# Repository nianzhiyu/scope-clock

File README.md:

# scope-clock
A digital clock using oscilloscope CRT display.
Derived from cathode corner's design: http://www.cathodecorner.com/sc200c.html

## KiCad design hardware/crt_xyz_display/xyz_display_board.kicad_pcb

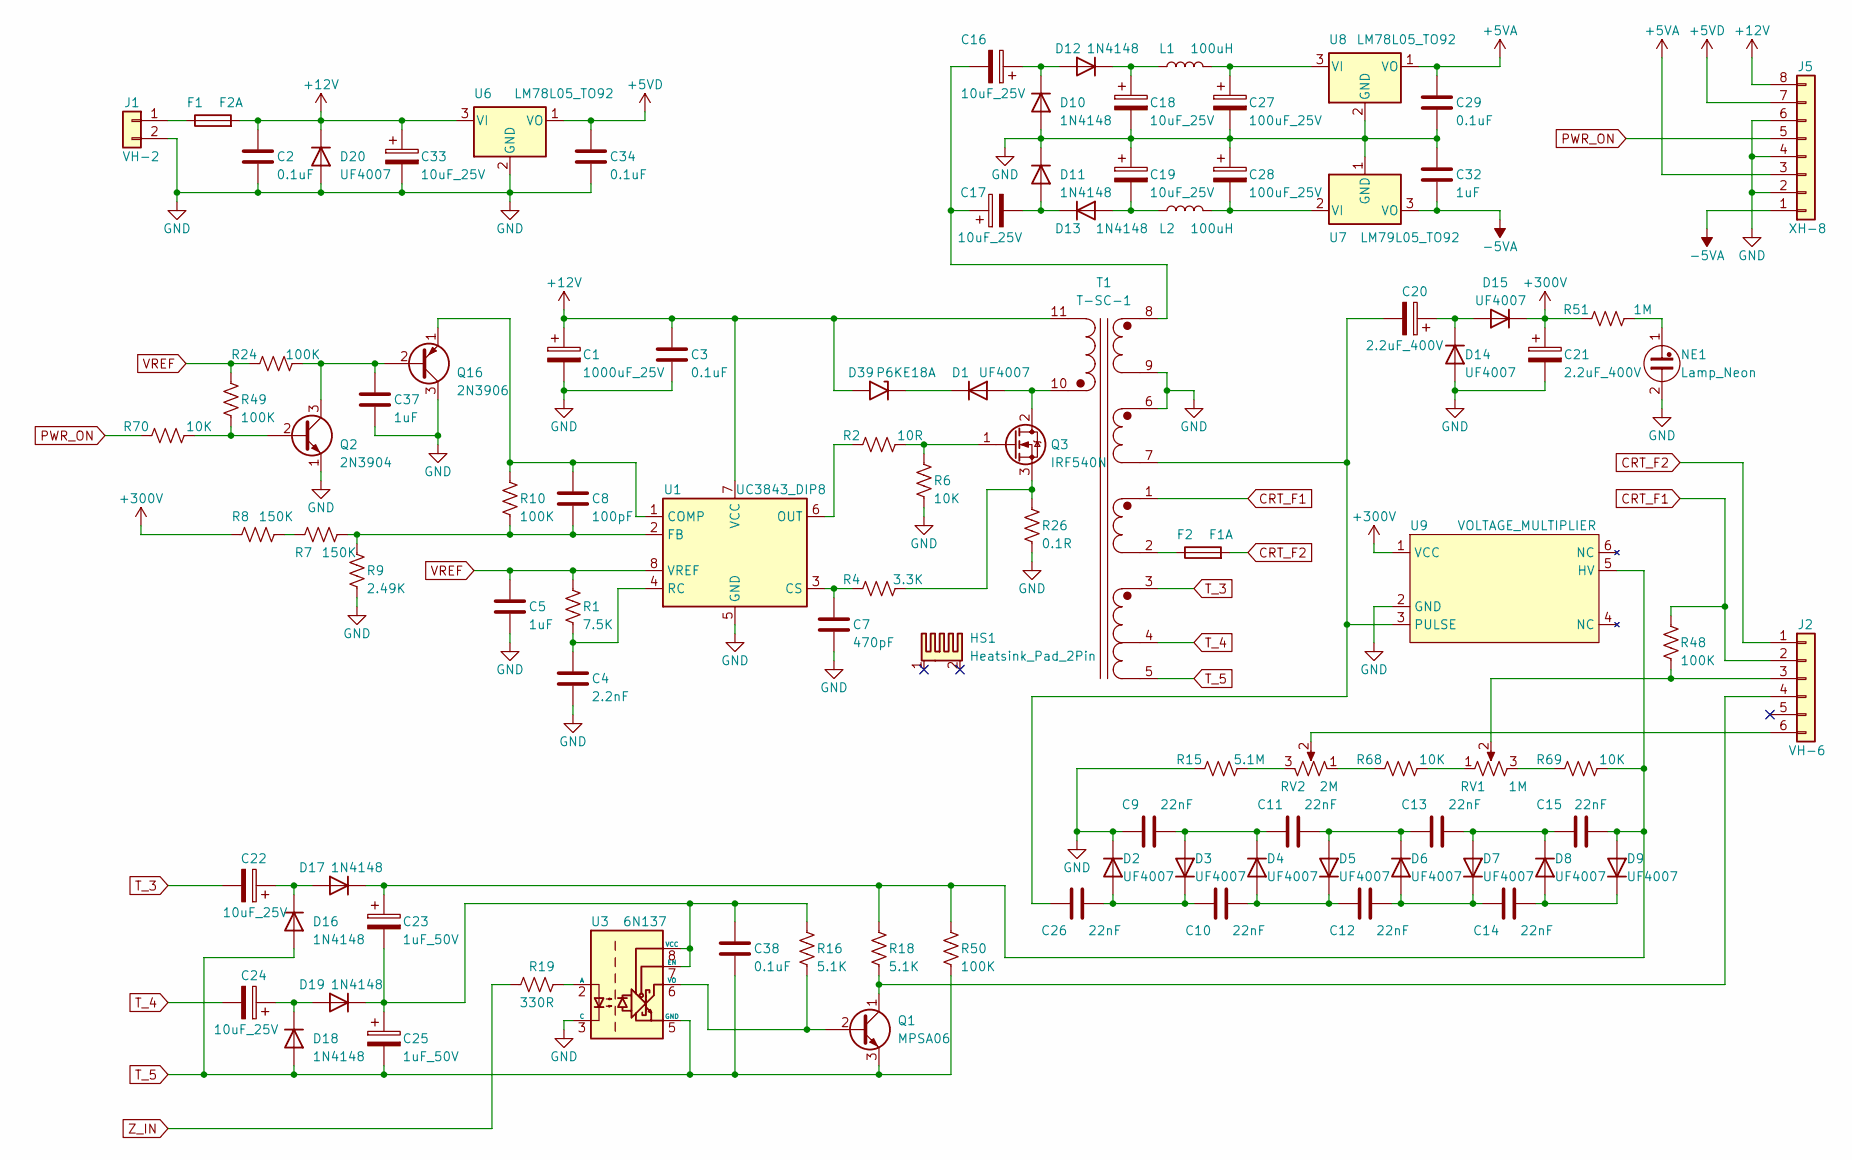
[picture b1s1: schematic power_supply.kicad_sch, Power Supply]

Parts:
C1: 1000uF_25V; CP_Radial_D10.0mm_P5.00mm
C2, C3, C29, C34, C38: 0.1uF; C_Rect_L5.5mm_W4.0mm_P5.00mm
C4: 2.2nF; C_Rect_L5.5mm_W4.0mm_P5.00mm
C5, C32, C37: 1uF; C_Rect_L5.5mm_W4.0mm_P5.00mm
C7: 470pF; C_Rect_L5.5mm_W4.0mm_P5.00mm
C8: 100pF; C_Rect_L5.5mm_W4.0mm_P5.00mm
C9, C10, C11, C12, C13, C14, C15, C26: 22nF; C_1206_3216Metric
C16, C17, C18, C19: 10uF_25V; CP_Radial_D6.3mm_P2.50mm
C20, C21: 2.2uF_400V; CP_Radial_D8.0mm_P3.50mm
C22, C24, C33: 10uF_25V; CP_Radial_D5.0mm_P2.50mm
C23, C25: 1uF_50V; CP_Radial_D5.0mm_P2.50mm
C27, C28: 100uF_25V; CP_Radial_D6.3mm_P2.50mm
D1, D2, D3, D4, D5, D6, D7, D8, D9, D14, D15, D20: UF4007; D_DO-41_SOD81_P7.62mm_Horizontal
D10, D11, D12, D13, D16, D17, D18, D19: 1N4148; DO-35-H6_8
D39: P6KE18A; D_DO-15_P10.16mm_Horizontal
F1: F2A; FUSE_D3.0mm_L8.3mm_P10.16mm
F2: F1A; FUSE_D3.0mm_L8.3mm_P10.16mm
HS1: Heatsink_Pad_2Pin; HS2-23_5X16X25
J1: VH-2; JST_VH_B2P-VH_1x02_P3.96mm_Vertical
J2: VH-6; JST_VH_B6P-VH_1x06_P3.96mm_Vertical
J5: XH-8; JST_XH_B8B-XH-A_1x08_P2.50mm_Vertical
L1, L2: 100uH; L_Radial_D5.5mm_P2.00mm
NE1: Lamp_Neon; NL_D5.0mm
Q1: MPSA06; TO-92L_Inline_Wide
Q2: 2N3904; TO-92_Inline
Q3: IRF540N; TO-220-3_Vertical
Q16: 2N3906; TO-92_Inline
R1: 7.5K; RES-H10_16-D2_5L7_5
R2: 10R; RES-H10_16-D2_5L7_5
R4: 3.3K; RES-H10_16-D2_5L7_5
R6, R68, R69, R70: 10K; RES-H10_16-D2_5L7_5
R7, R8: 150K; RES-H10_16-D2_5L7_5
R9: 2.49K; RES-H10_16-D2_5L7_5
R10, R24, R48, R49, R50: 100K; RES-H10_16-D2_5L7_5
R15: 5.1M; RES-H10_16-D2_5L7_5
R16, R18: 5.1K; RES-H10_16-D2_5L7_5
R19: 330R; RES-H10_16-D2_5L7_5
R26: 0.1R; R_Axial_DIN0516_L15.5mm_D5.0mm_P20.32mm_Horizontal
R51: 1M; RES-H10_16-D2_5L7_5
RV1: 1M; RP-3362S
RV2: 2M; RP-3362S
T1: T-SC-1
U1: UC3843_DIP8; DIP-8_W7.62mm
U3: 6N137; DIP-8_W7.62mm
U6, U8: LM78L05_TO92; TO-92_Inline_Wide
U7: LM79L05_TO92; TO-92_Inline_Wide
U9: VOLTAGE_MULTIPLIER; VM-SC-1

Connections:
+5VA: C29.1, J5.3, U8.1 (VO); also elsewhere on the board
+5VD: C34.1, J5.7, U6.1 (VO)
+12V: C1.1, C2.1, C3.1, C33.1, D20.1 (K), D39.2 (A2), F1.2, J5.8, T1.11, U1.7 (VCC), U6.3 (VI)
+300V: C21.1, D15.1 (K), R8.2, R51.1, U9.1 (VCC); also elsewhere on the board
-5VA: C32.2, J5.1, U7.3 (VO); also elsewhere on the board
CRT_F1: J2.2, R48.2, T1.1
CRT_F2: F2.2, J2.1
GND: C1.2, C2.2, C3.2, C4.2, C5.2, C7.2, C9.1, C18.2, C19.1, C21.2, C27.2, C28.1, C29.2, C32.1, C33.2, C34.2, C37.2, D2.1 (K), D10.2 (A), D11.1 (K), D14.2 (A), D20.2 (A), J1.2, J5.2, J5.4, J5.6, NE1.2, Q2.1 (E), Q16.3 (C), R6.2, R9.2, R15.1, R26.2, T1.6, T1.9, U1.5 (GND), U3.3 (C), U6.2 (GND), U7.1 (GND), U8.2 (GND), U9.2 (GND); also elsewhere on the board
unnamed: C4.1, R1.2, U1.4 (RC)
unnamed: C7.1, R4.1, U1.3 (CS)
unnamed: C8.1, Q16.1 (E), R10.1, U1.1 (COMP)
unnamed: C8.2, R7.1, R9.1, R10.2, U1.2 (FB)
unnamed: C10.1, C26.2, D2.2 (A), D3.1 (K)
unnamed: C10.2, C12.1, D4.2 (A), D5.1 (K)
unnamed: C9.2, C11.1, D3.2 (A), D4.1 (K)
unnamed: C11.2, C13.1, D5.2 (A), D6.1 (K)
unnamed: C12.2, C14.1, D6.2 (A), D7.1 (K)
unnamed: C13.2, C15.1, D7.2 (A), D8.1 (K)
unnamed: C14.2, D8.2 (A), D9.1 (K)
unnamed: C15.2, C23.1, D9.2 (A), D17.1 (K), R18.1, R50.1, R69.2, U9.5 (HV)
unnamed: C16.1, D10.1 (K), D12.2 (A)
unnamed: C16.2, C17.1, T1.8
unnamed: C17.2, D11.2 (A), D13.1 (K)
unnamed: C18.1, D12.1 (K), L1.1
unnamed: C19.2, D13.2 (A), L2.1
unnamed: C20.1, D14.1 (K), D15.2 (A)
unnamed: C20.2, C26.1, T1.7, U9.3 (PULSE)
unnamed: C22.1, D16.1 (K), D17.2 (A)
unnamed: C23.2, C25.1, C38.1, D19.1 (K), R16.1, U3.7 (EN), U3.8 (VCC)
unnamed: C24.1, D18.1 (K), D19.2 (A)
unnamed: C27.1, L1.2, U8.3 (VI)
unnamed: C28.2, L2.2, U7.2 (VI)
unnamed: C37.1, Q2.3 (C), Q16.2 (B), R24.2
unnamed: D1.1 (K), D39.1 (A1)
unnamed: D1.2 (A), Q3.2 (D), T1.10
unnamed: F1.1, J1.1
unnamed: F2.1, T1.2
unnamed: J2.3, R48.1, RV1.2
unnamed: J2.4, Q1.1 (C), R18.2
unnamed: J2.6, RV2.2
unnamed: NE1.1, R51.2
unnamed: Q1.2 (B), R16.2, U3.6 (VO)
unnamed: Q2.2 (B), R49.2, R70.2
unnamed: Q3.1 (G), R2.2, R6.1
unnamed: Q3.3 (S), R4.2, R26.1
unnamed: R2.1, U1.6 (OUT)
unnamed: R7.2, R8.1
unnamed: R15.2, RV2.3
unnamed: R19.1, U3.2 (A)
unnamed: R68.1, RV2.1
unnamed: R68.2, RV1.1
unnamed: R69.1, RV1.3
PWR_ON: J5.5, R70.1
T_3: C22.2, T1.3
T_4: C24.2, T1.4
T_5: C25.2, C38.2, D16.2 (A), D18.2 (A), Q1.3 (E), R50.2, T1.5, U3.5 (GND)
VREF: C5.1, R1.1, R24.1, R49.1, U1.8 (VREF)
Z_IN: R19.2; also elsewhere on the board

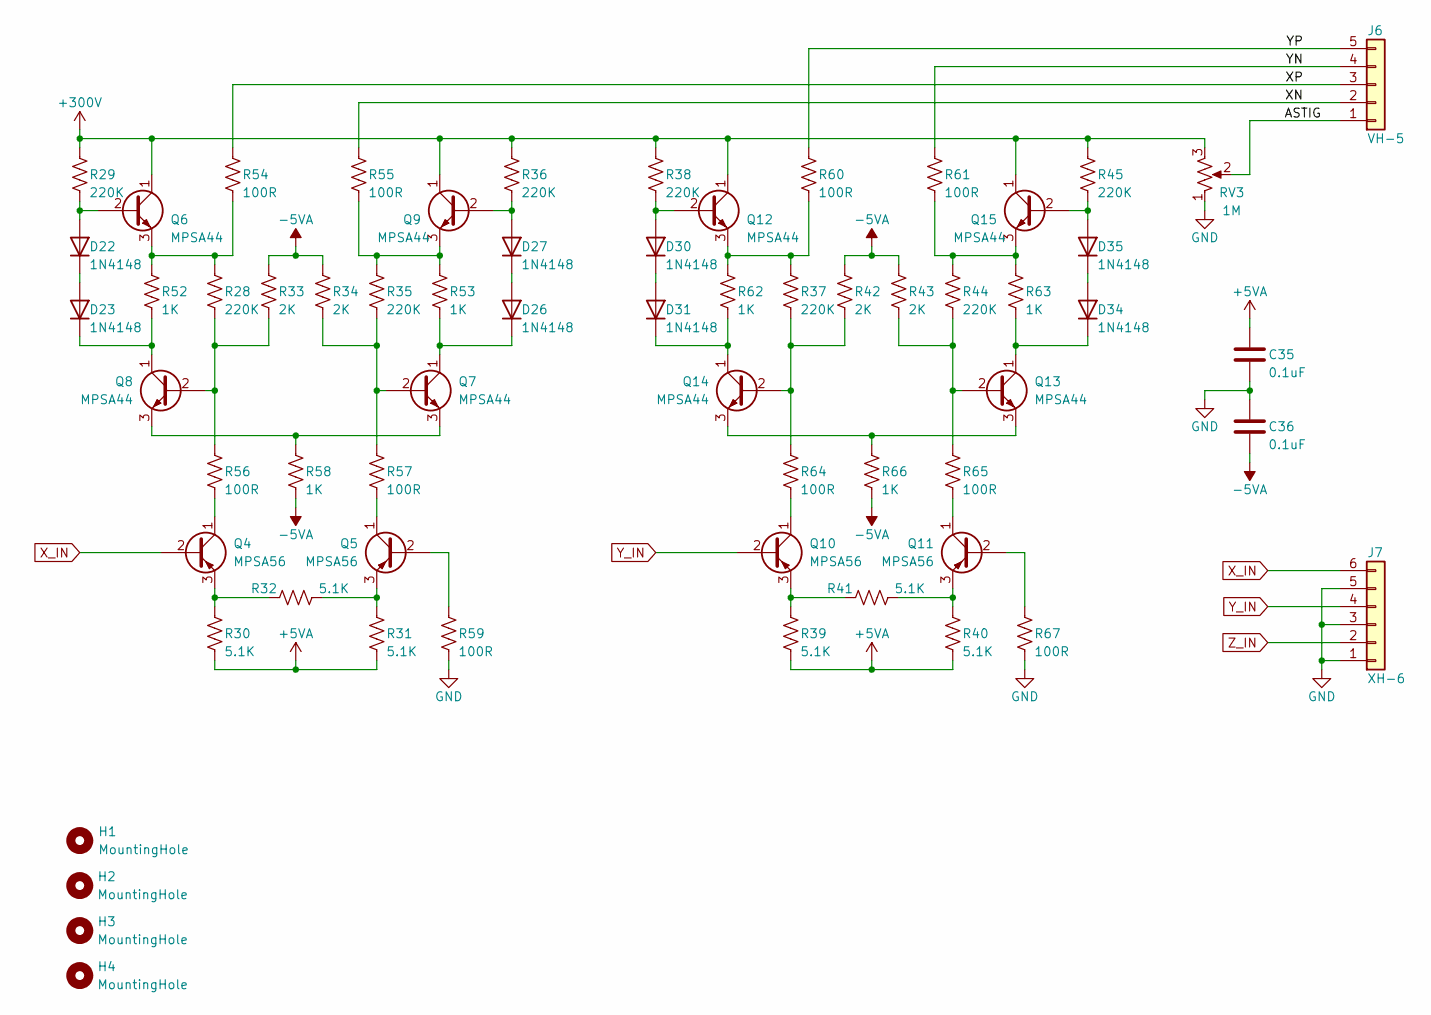
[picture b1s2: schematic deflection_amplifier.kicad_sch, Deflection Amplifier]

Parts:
C35, C36: 0.1uF; C_Rect_L5.5mm_W4.0mm_P5.00mm
D22, D23, D26, D27, D30, D31, D34, D35: 1N4148; DO-35-H6_8
H1, H2, H3, H4: MountingHole; MountingHole_3.2mm_M3
J6: VH-5; JST_VH_B5P-VH_1x05_P3.96mm_Vertical
J7: XH-6; JST_XH_B6B-XH-A_1x06_P2.50mm_Vertical
Q4, Q5, Q10, Q11: MPSA56; TO-92C
Q6, Q7, Q8, Q9, Q12, Q13, Q14, Q15: MPSA44; TO-92C
R28, R29, R35, R36, R37, R38, R44, R45: 220K; RES-H10_16-D2_5L7_5
R30, R31, R32, R39, R40, R41: 5.1K; RES-H10_16-D2_5L7_5
R33, R34, R42, R43: 2K; RES-H10_16-D2_5L7_5
R52, R53, R58, R62, R63, R66: 1K; RES-H10_16-D2_5L7_5
R54, R55, R56, R57, R59, R60, R61, R64, R65, R67: 100R; RES-H10_16-D2_5L7_5
RV3: 1M; RP-3362S

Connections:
+5VA: C35.1, R30.2, R31.2, R39.2, R40.2; also elsewhere on the board
+300V: Q6.1 (C), Q9.1 (C), Q12.1 (C), Q15.1 (C), R29.1, R36.1, R38.1, R45.1, RV3.3; also elsewhere on the board
-5VA: C36.2, R33.1, R34.1, R42.1, R43.1, R58.2, R66.2; also elsewhere on the board
/Deflection_Amplifier/ASTIG: J6.1, RV3.2
/Deflection_Amplifier/XN: J6.2, R55.1
/Deflection_Amplifier/XP: J6.3, R54.1
/Deflection_Amplifier/YN: J6.4, R61.1
/Deflection_Amplifier/YP: J6.5, R60.1
GND: C35.2, C36.1, J7.1, J7.3, J7.5, R59.2, R67.2, RV3.1; also elsewhere on the board
unnamed: D22.1 (K), D23.2 (A)
unnamed: D22.2 (A), Q6.2 (B), R29.2
unnamed: D23.1 (K), Q8.1 (C), R52.2
unnamed: D26.1 (K), Q7.1 (C), R53.2
unnamed: D26.2 (A), D27.1 (K)
unnamed: D27.2 (A), Q9.2 (B), R36.2
unnamed: D30.1 (K), D31.2 (A)
unnamed: D30.2 (A), Q12.2 (B), R38.2
unnamed: D31.1 (K), Q14.1 (C), R62.2
unnamed: D34.1 (K), Q13.1 (C), R63.2
unnamed: D34.2 (A), D35.1 (K)
unnamed: D35.2 (A), Q15.2 (B), R45.2
unnamed: Q4.1 (C), R56.2
unnamed: Q4.3 (E), R30.1, R32.1
unnamed: Q5.1 (C), R57.2
unnamed: Q5.2 (B), R59.1
unnamed: Q5.3 (E), R31.1, R32.2
unnamed: Q6.3 (E), R28.1, R52.1, R54.2
unnamed: Q7.2 (B), R34.2, R35.2, R57.1
unnamed: Q7.3 (E), Q8.3 (E), R58.1
unnamed: Q8.2 (B), R28.2, R33.2, R56.1
unnamed: Q9.3 (E), R35.1, R53.1, R55.2
unnamed: Q10.1 (C), R64.2
unnamed: Q10.3 (E), R39.1, R41.1
unnamed: Q11.1 (C), R65.2
unnamed: Q11.2 (B), R67.1
unnamed: Q11.3 (E), R40.1, R41.2
unnamed: Q12.3 (E), R37.1, R60.2, R62.1
unnamed: Q13.2 (B), R43.2, R44.2, R65.1
unnamed: Q13.3 (E), Q14.3 (E), R66.1
unnamed: Q14.2 (B), R37.2, R42.2, R64.1
unnamed: Q15.3 (E), R44.1, R61.2, R63.1
X_IN: J7.6, Q4.2 (B)
Y_IN: J7.4, Q10.2 (B)
Z_IN: J7.2; also elsewhere on the board

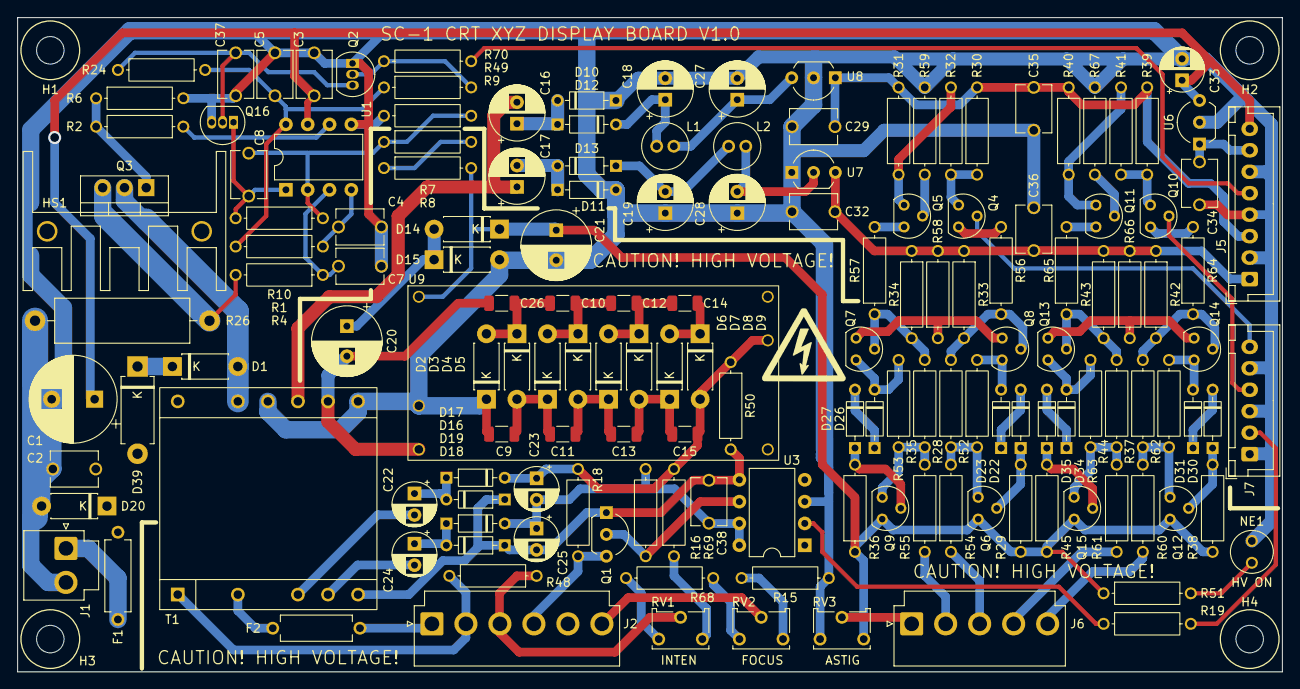
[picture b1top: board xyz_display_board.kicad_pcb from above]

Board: 2 copper layers, 147.3 x 76.2 mm, 160 parts (0 on the bottom side), 97 nets.

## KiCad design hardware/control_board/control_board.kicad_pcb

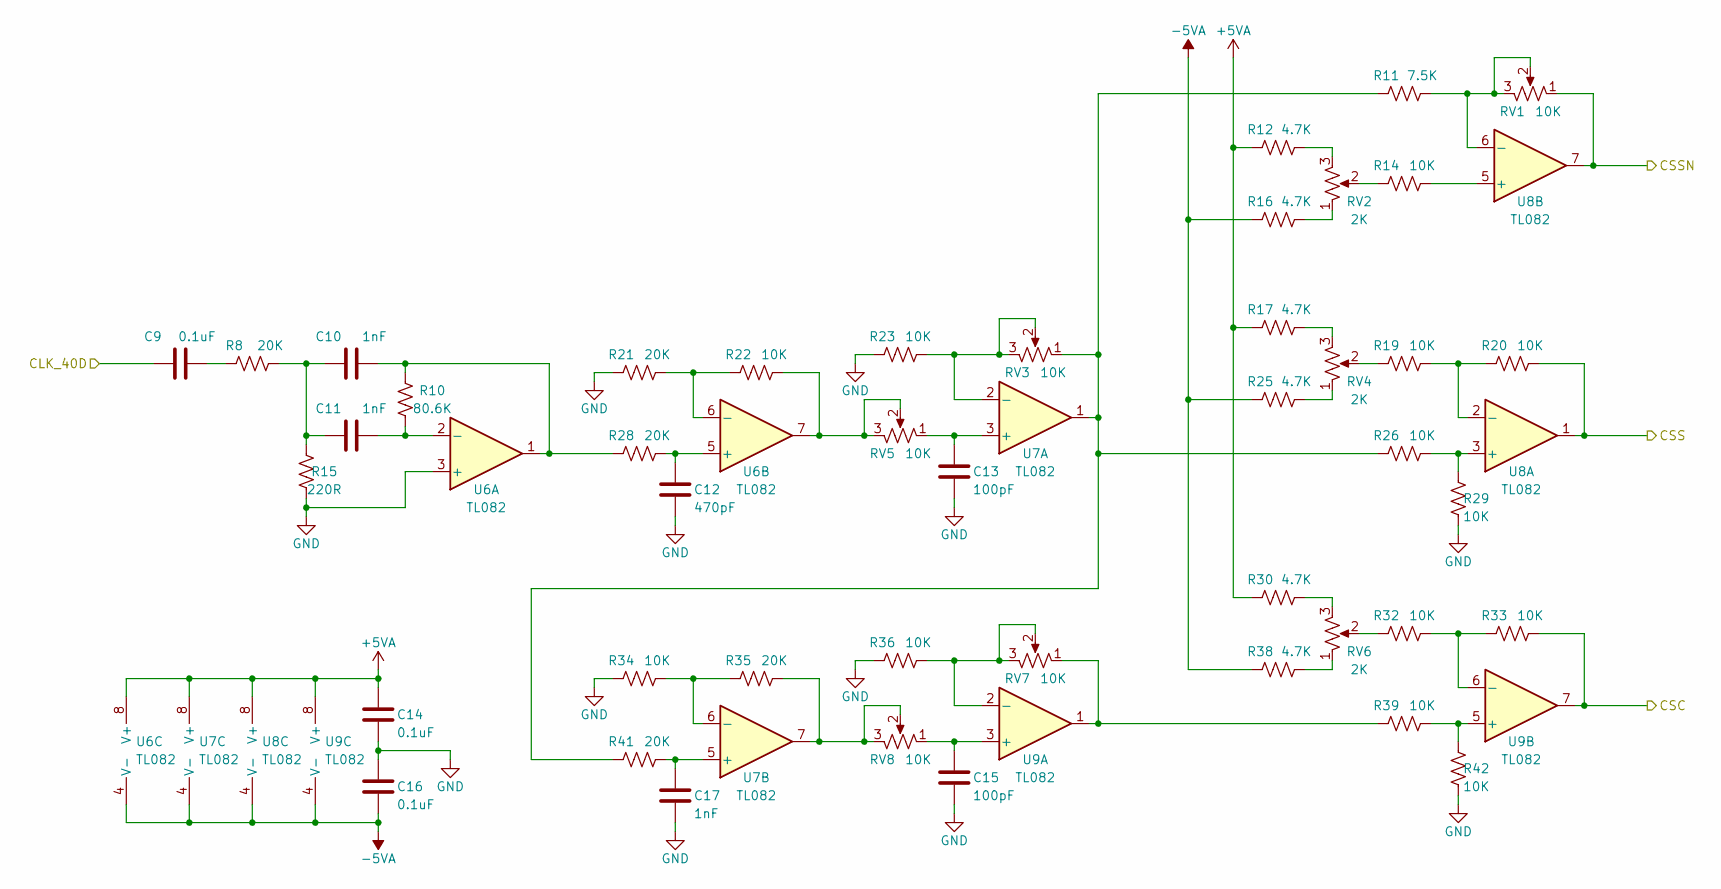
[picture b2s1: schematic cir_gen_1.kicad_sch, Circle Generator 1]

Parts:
C9, C14, C16: 0.1uF; C_Rect_L5.5mm_W4.0mm_P5.00mm
C10, C11, C17: 1nF; C_Rect_L5.5mm_W4.0mm_P5.00mm
C12: 470pF; C_Rect_L5.5mm_W4.0mm_P5.00mm
C13, C15: 100pF; C_Rect_L5.5mm_W4.0mm_P5.00mm
R8, R21, R28, R35, R41: 20K; RES-H10_16-D2_5L7_5
R10: 80.6K; RES-H10_16-D2_5L7_5
R11: 7.5K; RES-H10_16-D2_5L7_5
R12, R16, R17, R25, R30, R38: 4.7K; RES-H10_16-D2_5L7_5
R14, R19, R20, R22, R23, R26, R29, R32, R33, R34, R36, R39, R42: 10K; RES-H10_16-D2_5L7_5
R15: 220R; RES-H10_16-D2_5L7_5
RV1, RV3, RV5, RV7, RV8: 10K; RP-3362S
RV2, RV4, RV6: 2K; RP-3362S
U6, U7, U8, U9: TL082; DIP-8_W7.62mm_Socket

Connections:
+5VA: C14.1, R12.2, R17.2, R30.2, U6.8 (V+), U7.8 (V+), U8.8 (V+), U9.8 (V+); also elsewhere on the board
-5VA: C16.2, R16.2, R25.2, R38.2, U6.4 (V-), U7.4 (V-), U8.4 (V-), U9.4 (V-); also elsewhere on the board
/Circle_Generator_1/CLK_40D: C9.1; also elsewhere on the board
/Circle_Generator_1/CSC: R33.1, U9.7; also elsewhere on the board
/Circle_Generator_1/CSSN: RV1.1, U8.7; also elsewhere on the board
/Circle_Generator_2/VREFA: R20.1, U8.1; also elsewhere on the board
GND: C12.2, C13.2, C14.2, C15.2, C16.1, C17.2, R15.1, R21.2, R23.2, R29.2, R34.2, R36.2, R42.2, U6.3 (+); also elsewhere on the board
unnamed: C9.2, R8.2
unnamed: C10.1, C11.1, R8.1, R15.2
unnamed: C10.2, R10.2, R28.2, U6.1
unnamed: C11.2, R10.1, U6.2 (-)
unnamed: C12.1, R28.1, U6.5 (+)
unnamed: C13.1, RV5.1, U7.3 (+)
unnamed: C15.1, RV8.1, U9.3 (+)
unnamed: C17.1, R41.1, U7.5 (+)
unnamed: R11.1, RV1.2, RV1.3, U8.6 (-)
unnamed: R11.2, R26.2, R41.2, RV3.1, U7.1
unnamed: R12.1, RV2.3
unnamed: R14.1, U8.5 (+)
unnamed: R14.2, RV2.2
unnamed: R16.1, RV2.1
unnamed: R17.1, RV4.3
unnamed: R19.1, R20.2, U8.2 (-)
unnamed: R19.2, RV4.2
unnamed: R21.1, R22.2, U6.6 (-)
unnamed: R22.1, RV5.2, RV5.3, U6.7
unnamed: R23.1, RV3.2, RV3.3, U7.2 (-)
unnamed: R25.1, RV4.1
unnamed: R26.1, R29.1, U8.3 (+)
unnamed: R30.1, RV6.3
unnamed: R32.1, R33.2, U9.6 (-)
unnamed: R32.2, RV6.2
unnamed: R34.1, R35.2, U7.6 (-)
unnamed: R35.1, RV8.2, RV8.3, U7.7
unnamed: R36.1, RV7.2, RV7.3, U9.2 (-)
unnamed: R38.1, RV6.1
unnamed: R39.1, R42.1, U9.5 (+)
unnamed: R39.2, RV7.1, U9.1

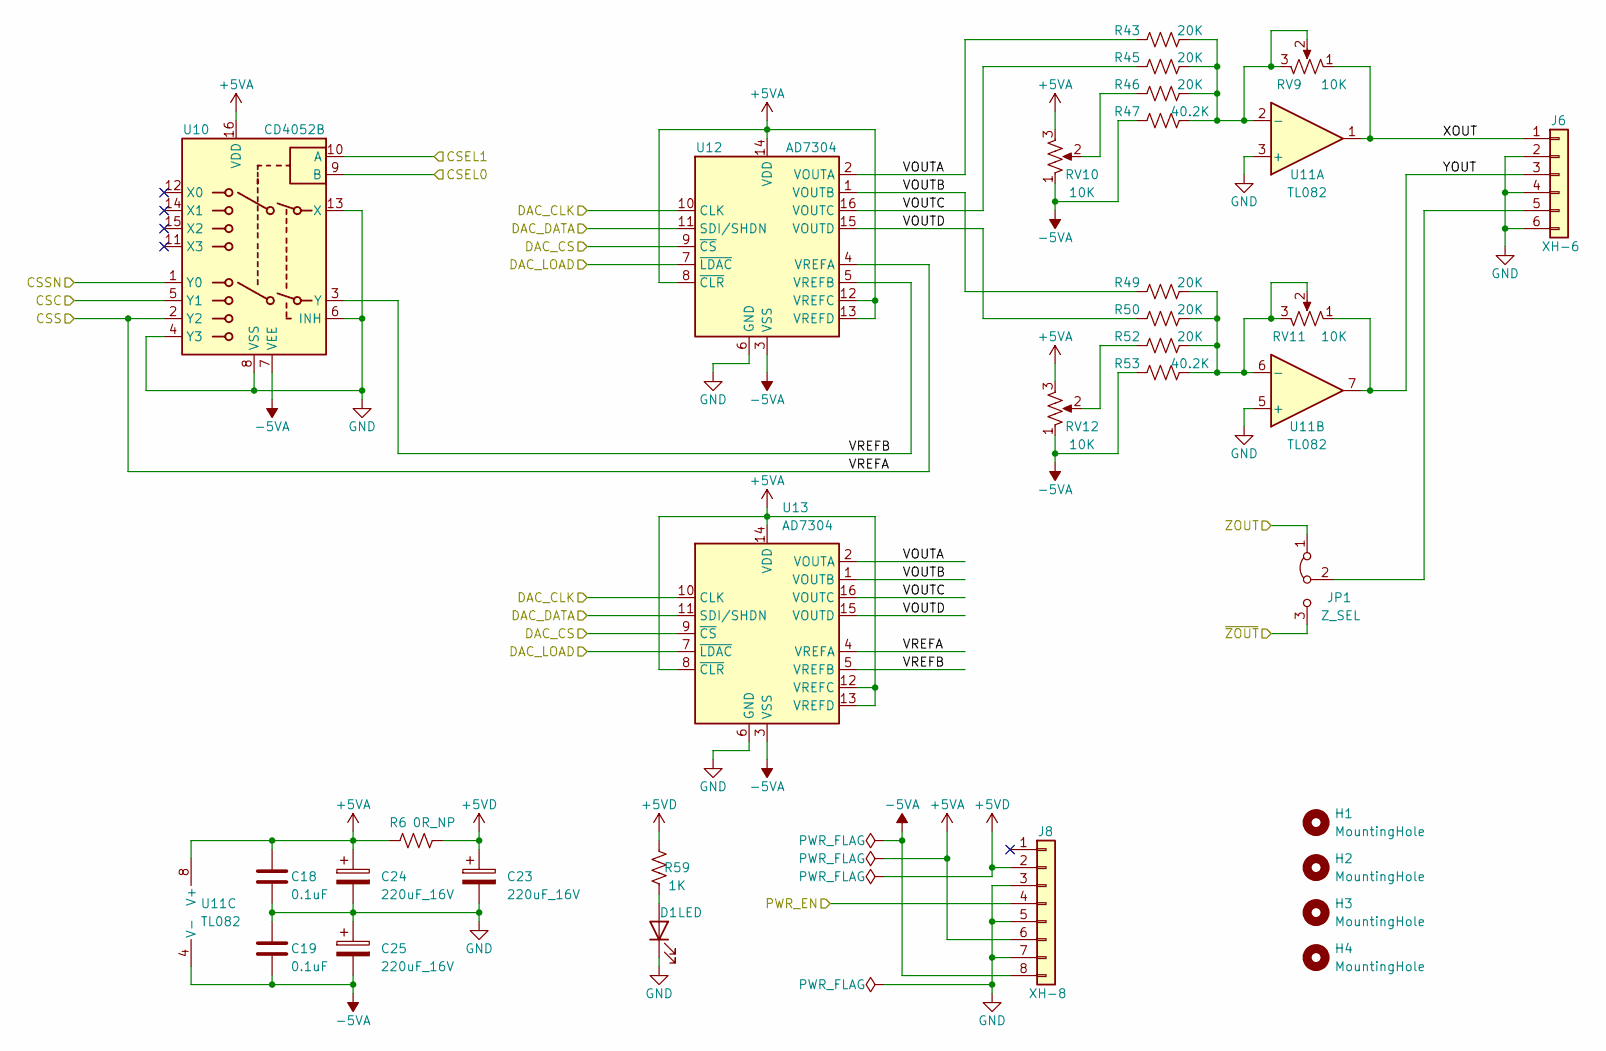
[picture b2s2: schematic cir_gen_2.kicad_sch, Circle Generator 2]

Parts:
C18, C19: 0.1uF; C_Rect_L5.5mm_W4.0mm_P5.00mm
C23, C24, C25: 220uF_16V; CP_Radial_D6.3mm_P2.50mm
D1: LED; LED_D3.0mm
H1, H2, H3, H4: MountingHole; MountingHole_3.2mm_M3
J6: XH-6; JST_XH_B6B-XH-A_1x06_P2.50mm_Vertical
J8: XH-8; JST_XH_B8B-XH-A_1x08_P2.50mm_Vertical
JP1: Z_SEL; PinHeader_1x03_P2.54mm_Vertical
R6: 0R_NP; RES-H10_16-D2_5L7_5
R43, R45, R46, R49, R50, R52: 20K; RES-H10_16-D2_5L7_5
R47, R53: 40.2K; RES-H10_16-D2_5L7_5
R59: 1K; RES-H10_16-D2_5L7_5
RV9, RV10, RV11, RV12: 10K; RP-3362S
U10: CD4052B; DIP-16_W7.62mm_Socket
U11: TL082; DIP-8_W7.62mm_Socket
U12: AD7304; TSSOP-16_4.4x5mm_P0.65mm
U13: AD7304; SOIC-16W_7.5x10.3mm_P1.27mm

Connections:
+5VA: C18.1, C24.1, J8.6, R6.2, RV10.3, RV12.3, U10.16 (VDD), U11.8 (V+), U12.8 (~CLR), U12.12 (VREFC), U12.13 (VREFD), U12.14 (VDD), U13.8 (~CLR), U13.12 (VREFC), U13.13 (VREFD), U13.14 (VDD); also elsewhere on the board
+5VD: C23.1, J8.2, R6.1, R59.2; also elsewhere on the board
-5VA: C19.2, C25.2, J8.8, R47.2, R53.2, RV10.1, RV12.1, U10.7 (VEE), U11.4 (V-), U12.3 (VSS), U13.3 (VSS); also elsewhere on the board
/Circle_Generator_1/CSC: U10.5 (Y1); also elsewhere on the board
/Circle_Generator_1/CSSN: U10.1 (Y0); also elsewhere on the board
/Circle_Generator_2/CSEL0: U10.9 (B); also elsewhere on the board
/Circle_Generator_2/CSEL1: U10.10 (A); also elsewhere on the board
/Circle_Generator_2/DAC_CLK: U12.10 (CLK), U13.10 (CLK); also elsewhere on the board
/Circle_Generator_2/DAC_CS: U12.9 (~CS), U13.9 (~CS); also elsewhere on the board
/Circle_Generator_2/DAC_DATA: U12.11 (SDI/SHDN), U13.11 (SDI/SHDN); also elsewhere on the board
/Circle_Generator_2/DAC_LOAD: U12.7 (~LDAC), U13.7 (~LDAC); also elsewhere on the board
/Circle_Generator_2/PWR_EN: J8.4; also elsewhere on the board
/Circle_Generator_2/VOUTA: R43.2, U12.2 (VOUTA), U13.2 (VOUTA)
/Circle_Generator_2/VOUTB: R49.2, U12.1 (VOUTB), U13.1 (VOUTB)
/Circle_Generator_2/VOUTC: R45.2, U12.16 (VOUTC), U13.16 (VOUTC)
/Circle_Generator_2/VOUTD: R50.2, U12.15 (VOUTD), U13.15 (VOUTD)
/Circle_Generator_2/VREFA: U10.2 (Y2), U12.4 (VREFA), U13.4 (VREFA); also elsewhere on the board
/Circle_Generator_2/VREFB: U10.3 (Y), U12.5 (VREFB), U13.5 (VREFB)
/Circle_Generator_2/XOUT: J6.1, RV9.1, U11.1
/Circle_Generator_2/YOUT: J6.3, RV11.1, U11.7
/Circle_Generator_2/ZOUT: JP1.1 (A); also elsewhere on the board
/Circle_Generator_2/~ZOUT: JP1.3 (B); also elsewhere on the board
GND: C18.2, C19.1, C23.2, C24.2, C25.1, D1.2 (K), J6.2, J6.4, J6.6, J8.3, J8.5, J8.7, U10.4 (Y3), U10.6 (INH), U10.8 (VSS), U10.13 (X), U11.3 (+), U11.5 (+), U12.6 (GND), U13.6 (GND); also elsewhere on the board
unnamed: D1.1 (A), R59.1
unnamed: J6.5, JP1.2 (C)
unnamed: R43.1, R45.1, R46.1, R47.1, RV9.2, RV9.3, U11.2 (-)
unnamed: R46.2, RV10.2
unnamed: R49.1, R50.1, R52.1, R53.1, RV11.2, RV11.3, U11.6 (-)
unnamed: R52.2, RV12.2

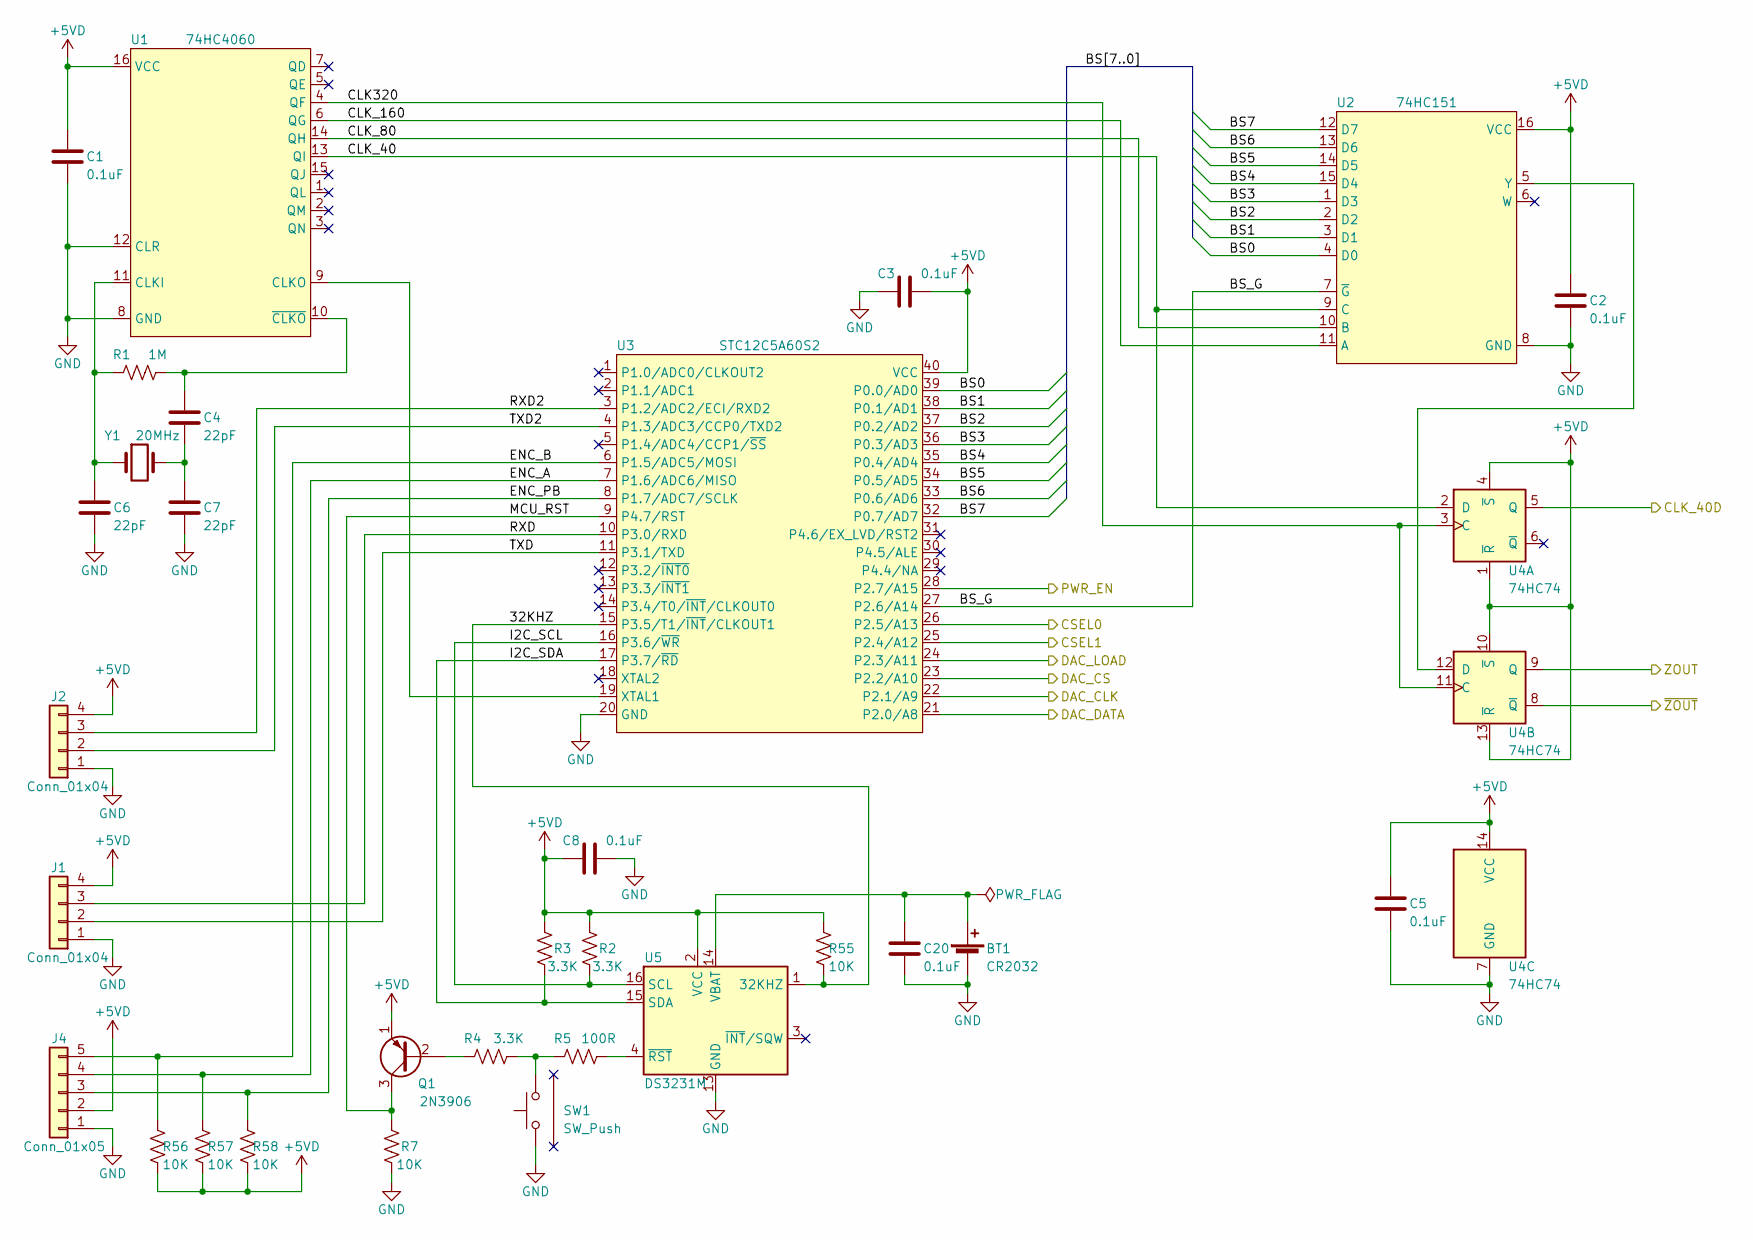
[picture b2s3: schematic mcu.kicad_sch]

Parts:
BT1: CR2032; BAT2-CR2032
C1, C2, C3, C5, C8, C20: 0.1uF; C_Rect_L5.5mm_W4.0mm_P5.00mm
C4, C6, C7: 22pF; C_Rect_L5.5mm_W4.0mm_P5.00mm
J1, J2: Conn_01x04; PinHeader_1x04_P2.54mm_Vertical
J4: Conn_01x05; PinHeader_1x05_P2.54mm_Vertical
Q1: 2N3906; TO-92_Inline
R1: 1M; RES-H10_16-D2_5L7_5
R2, R3, R4: 3.3K; RES-H10_16-D2_5L7_5
R5: 100R; RES-H10_16-D2_5L7_5
R7, R55, R56, R57, R58: 10K; RES-H10_16-D2_5L7_5
SW1: SW_Push; SW-TC2-SG-5_85
U1: 74HC4060; DIP-16_W7.62mm_Socket
U2: 74HC151; DIP-16_W7.62mm_Socket
U3: STC12C5A60S2; DIP-40_W15.24mm_Socket
U4: 74HC74; DIP-14_W7.62mm_Socket
U5: DS3231M; SOIC-16W_7.5x10.3mm_P1.27mm
Y1: 20MHz; Crystal_HC49-U_Vertical

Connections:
+5VD: C1.1, C2.1, C3.2, C5.1, C8.1, J1.4, J2.4, J4.2, Q1.1 (E), R2.2, R3.2, R55.2, R56.1, R57.1, R58.1, U1.16 (VCC), U2.16 (VCC), U3.40 (VCC), U4.1 (~R), U4.4 (~S), U4.10 (~S), U4.13 (~R), U4.14 (VCC), U5.2 (VCC); also elsewhere on the board
/Circle_Generator_1/CLK_40D: U4.5 (Q); also elsewhere on the board
/Circle_Generator_2/CSEL0: U3.26 (P2.5/A13); also elsewhere on the board
/Circle_Generator_2/CSEL1: U3.25 (P2.4/A12); also elsewhere on the board
/Circle_Generator_2/DAC_CLK: U3.22 (P2.1/A9); also elsewhere on the board
/Circle_Generator_2/DAC_CS: U3.23 (P2.2/A10); also elsewhere on the board
/Circle_Generator_2/DAC_DATA: U3.21 (P2.0/A8); also elsewhere on the board
/Circle_Generator_2/DAC_LOAD: U3.24 (P2.3/A11); also elsewhere on the board
/Circle_Generator_2/PWR_EN: U3.28 (P2.7/A15); also elsewhere on the board
/Circle_Generator_2/ZOUT: U4.9 (Q); also elsewhere on the board
/Circle_Generator_2/~ZOUT: U4.8 (~Q); also elsewhere on the board
/MCU/32KHZ: R55.1, U3.15 (P3.5/T1/~INT/CLKOUT1), U5.1 (32KHZ)
/MCU/BS0: U2.4 (D0), U3.39 (P0.0/AD0)
/MCU/BS1: U2.3 (D1), U3.38 (P0.1/AD1)
/MCU/BS2: U2.2 (D2), U3.37 (P0.2/AD2)
/MCU/BS3: U2.1 (D3), U3.36 (P0.3/AD3)
/MCU/BS4: U2.15 (D4), U3.35 (P0.4/AD4)
/MCU/BS5: U2.14 (D5), U3.34 (P0.5/AD5)
/MCU/BS6: U2.13 (D6), U3.33 (P0.6/AD6)
/MCU/BS7: U2.12 (D7), U3.32 (P0.7/AD7)
/MCU/BS_G: U2.7 (~G), U3.27 (P2.6/A14)
/MCU/CLK320: U1.4 (QF), U4.3 (C), U4.11 (C)
/MCU/CLK_40: U1.13 (QI), U2.9 (C), U4.2 (D)
/MCU/CLK_80: U1.14 (QH), U2.10 (B)
/MCU/CLK_160: U1.6 (QG), U2.11 (A)
/MCU/ENC_A: J4.4, R57.2, U3.7 (P1.6/ADC6/MISO)
/MCU/ENC_B: J4.5, R56.2, U3.6 (P1.5/ADC5/MOSI)
/MCU/ENC_PB: J4.3, R58.2, U3.8 (P1.7/ADC7/SCLK)
/MCU/I2C_SCL: R2.1, U3.16 (P3.6/~WR), U5.16 (SCL)
/MCU/I2C_SDA: R3.1, U3.17 (P3.7/~RD), U5.15 (SDA)
/MCU/MCU_RST: Q1.3 (C), R7.2, U3.9 (P4.7/RST)
/MCU/RXD: J1.3, U3.10 (P3.0/RXD)
/MCU/RXD2: J2.3, U3.3 (P1.2/ADC2/ECI/RXD2)
/MCU/TXD: J1.2, U3.11 (P3.1/TXD)
/MCU/TXD2: J2.2, U3.4 (P1.3/ADC3/CCP0/TXD2)
GND: BT1.2 (-), C1.2, C2.2, C3.1, C5.2, C6.2, C7.2, C8.2, C20.2, J1.1, J2.1, J4.1, R7.1, SW1.1, U1.8 (GND), U1.12 (CLR), U2.8 (GND), U3.20 (GND), U4.7 (GND), U5.5 (GND), U5.6 (GND), U5.7 (GND), U5.8 (GND), U5.9 (GND), U5.10 (GND), U5.11 (GND), U5.12 (GND), U5.13 (GND); also elsewhere on the board
unnamed: BT1.1 (+), C20.1, U5.14 (VBAT)
unnamed: C4.1, R1.2, U1.10 (~CLKO)
unnamed: C4.2, C7.1, Y1.2
unnamed: C6.1, R1.1, U1.11 (CLKI), Y1.1
unnamed: Q1.2 (B), R4.1
unnamed: R4.2, R5.1, SW1.2
unnamed: R5.2, U5.4 (~RST)
unnamed: U1.9 (CLKO), U3.19 (XTAL1)
unnamed: U2.5 (Y), U4.12 (D)

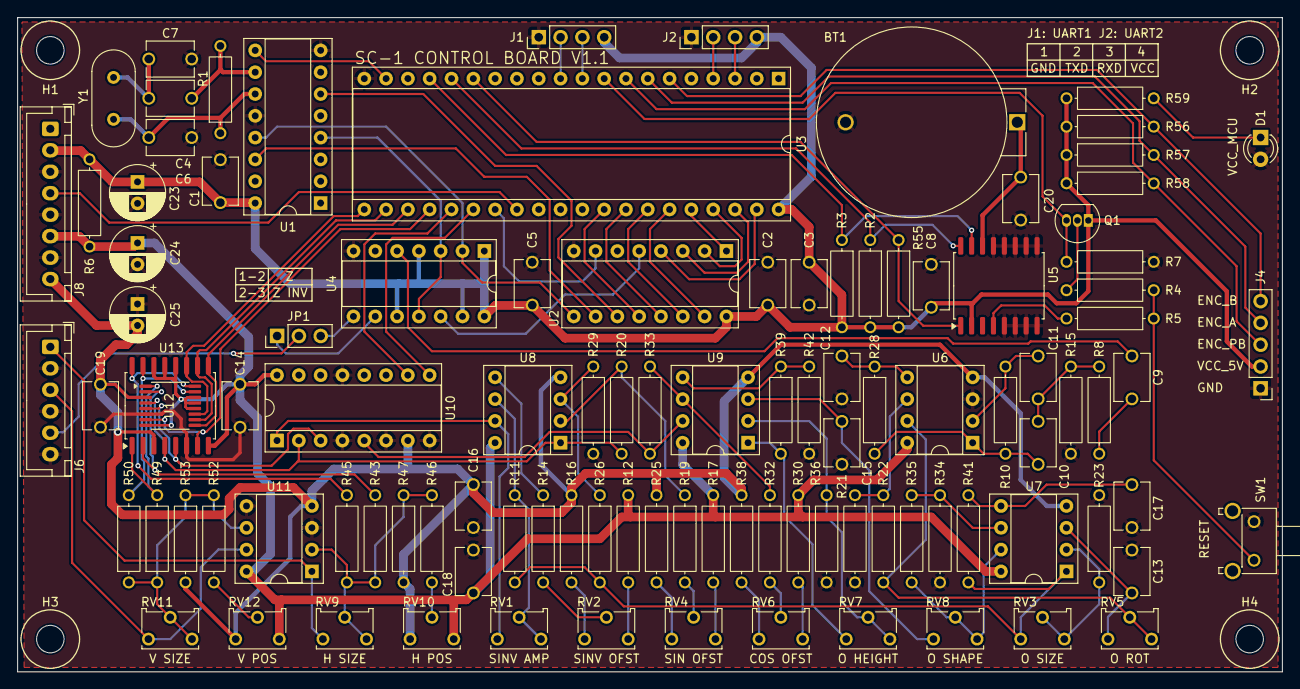
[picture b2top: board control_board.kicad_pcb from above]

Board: 2 copper layers, 147.3 x 76.2 mm, 110 parts (0 on the bottom side), 94 nets.

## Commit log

2024-08-28 add board design files
